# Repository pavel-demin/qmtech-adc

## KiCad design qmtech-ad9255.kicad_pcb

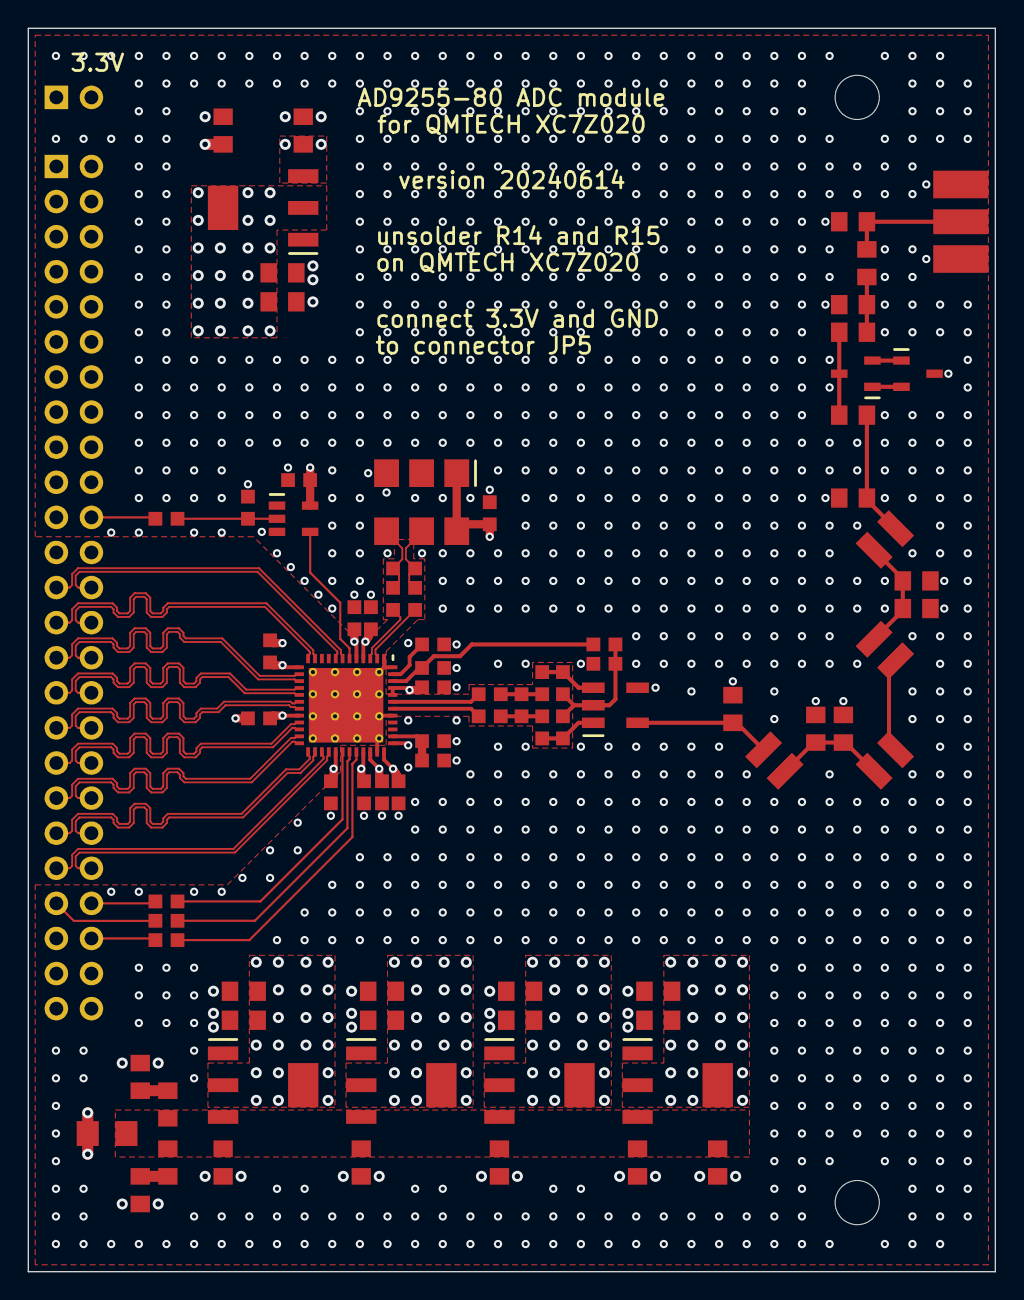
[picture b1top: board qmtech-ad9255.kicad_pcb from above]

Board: 4 copper layers, 70.0 x 90.0 mm, 85 parts (1 on the bottom side), 62 nets.

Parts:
C1, C2, C3, C4, C5, C6, C7, C8, C9, C10, C11, C12, C13, C14, C15, C16, C17, C30: 0603
C18, C19, C20, C21, C22, C23, C24, C25, C26, C27, C28, C29, C33, C34, C35, C36, C37, C38, C39, C40: 0805
CN1: SMA-EDGE
CN2: 2x25
CN3: 1x2
D1, D2: SOT23-3
FB1: 1206
H1, H2: M3
IC1: LFCSP48
IC2, IC3, IC4, IC5, IC6: SOT223-3
IC7: SOT23-5
L1, L2, L3, L4: 1008
R1, R2, R3, R4, R5, R6, R7, R8, R9, R10, R11, R12, R13, R14: 0603
R15, R16, R17, R18, R19, R20, R21, R22, R23, R24, R25, R26: 0805
T1: AT224
Y1: SMD7050-6P

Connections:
5V: C18.1, C20.1, C22.1, C24.1, C28.1, C29.1, FB1.2, IC2.3, IC3.3, IC4.3, IC5.3, R17.1
AIN+: IC1.42, R6.2
AIN-: IC1.43, R7.2
ATT1: CN1.1, R24.1, R25.1
ATT2: C33.1, R24.2, R26.1
AVDD: C6.1, C7.1, C8.1, C9.1, C10.1, C23.1, IC1.4, IC1.5, IC1.34, IC1.36, IC1.44, IC1.45, IC4.2, R20.1
CLK+: C17.1, R9.2, Y1.5
CLK-: C16.1, R9.1, Y1.4
CLKN: C16.2, IC1.3
CLKP: C17.2, IC1.2
CSB1: CN2.46, R12.1
CSB2: IC1.32, R12.2
CVDD: C15.1, C25.1, IC5.2, R21.1, Y1.1, Y1.6
D1N: CN2.27, IC1.11
D1P: CN2.28, IC1.12
D2N: CN2.29, IC1.14
D2P: CN2.30, IC1.15
D3N: CN2.31, IC1.16
D3P: CN2.32, IC1.17
D4N: CN2.33, IC1.18
D4P: CN2.34, IC1.19
D5N: CN2.35, IC1.21
D5P: CN2.36, IC1.22
D6N: CN2.37, IC1.23
D6P: CN2.38, IC1.24
D7N: CN2.39, IC1.25
D7P: CN2.40, IC1.26
DCON: CN2.25, IC1.7
DCOP: CN2.26, IC1.8
DMP1: C28.2, R15.1
DMP2: C29.2, R16.1
DVDD: C12.1, C13.1, C14.1, C19.1, C30.1, IC1.13, IC1.20, IC1.29, IC2.2, IC7.5, R18.1
FLT1: C34.2, C35.1, L1.1
FLT2: C36.1, C37.1, L1.2, L2.1
FLT3: L2.2, L3.1
FLT4: C38.1, C39.1, L3.2, L4.1
FLT5: C40.1, L4.2, T1.6
FLT+: C3.1, R4.2, R6.1
FLT-: C3.2, R5.2, R7.1
GND: C1.2, C2.2, C4.2, C5.2, C6.2, C7.2, C8.2, C9.2, C10.2, C11.2, C12.2, C13.2, C14.2, C15.2, C18.2, C19.2, C20.2, C21.2, C22.2, C23.2, C24.2, C25.2, C26.2, C27.2, C30.2, C35.2, C36.2, C37.2, C38.2, C39.2, C40.2, CN1.2, CN2.1, CN2.2, CN2.47, CN2.48, CN3.1, D2.3, IC1.0, IC1.1, IC1.35, IC1.37, IC1.41, IC1.48, IC2.1, IC3.1, IC4.1, IC5.1, IC6.1, IC7.3, R8.2, R11.2, R15.2, R16.2, R17.2, R18.2, R19.2, R20.2, R21.2, R22.2, R23.2, R25.2, R26.2, T1.4, Y1.3
OEB1: CN2.22, R10.1
OEB2: IC7.2, R10.2, R11.1
OEB3: IC1.6, IC7.4
ORN: CN2.41, IC1.27
ORP: CN2.42, IC1.28
RBIAS: IC1.47, R8.1
SCLK1: CN2.43, R13.1
SCLK2: IC1.31, R13.2
SDIO1: CN2.44, R14.1
SDIO2: IC1.30, R14.2
SEC+: R2.1, R4.1, T1.1
SEC-: R3.1, R5.1, T1.3
SVDD: C11.1, C21.1, IC1.33, IC3.2, R19.1
TVS1: C33.2, C34.1, D1.3
TVS2: D1.1, D2.2
TVS3: D1.2, D2.1
VCCO25: C27.1, CN2.3, CN2.4, IC6.2, R23.1
VCM1: C1.1, IC1.46, R1.1
VCM2: C2.1, R1.2, R2.2, R3.2, T1.2
VIN1: CN2.49, CN2.50, FB1.1
VIN2: C26.1, CN3.2, IC6.3, R22.1
VREF: C4.1, C5.1, IC1.38

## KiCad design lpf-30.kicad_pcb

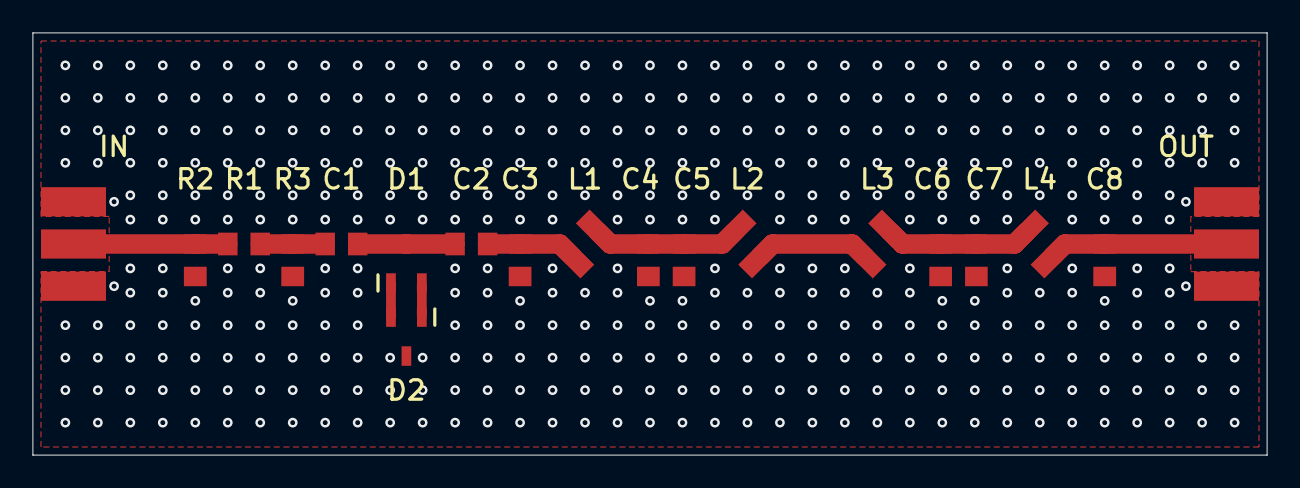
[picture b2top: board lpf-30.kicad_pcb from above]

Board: 2 copper layers, 76.0 x 26.0 mm, 19 parts (0 on the bottom side), 11 nets.

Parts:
C1, C2, C3, C4, C5, C6, C7, C8: 0805
D1, D2: SOT23-3
IN: SMA-EDGE
L1, L2, L3, L4: 1008
OUT: SMA-EDGE
R1, R2, R3: 0805

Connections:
ATT1: IN.1, R1.1, R2.1
ATT2: C1.1, R1.2, R3.1
FLT1: C2.2, C3.1, L1.1
FLT2: C4.1, C5.1, L1.2, L2.1
FLT3: L2.2, L3.1
FLT4: C6.1, C7.1, L3.2, L4.1
FLT5: C8.1, L4.2, OUT.1
GND: C3.2, C4.2, C5.2, C6.2, C7.2, C8.2, D2.3, IN.2, OUT.2, R2.2, R3.2
TVS1: C1.2, C2.1, D1.3
TVS2: D1.1, D2.2
TVS3: D1.2, D2.1

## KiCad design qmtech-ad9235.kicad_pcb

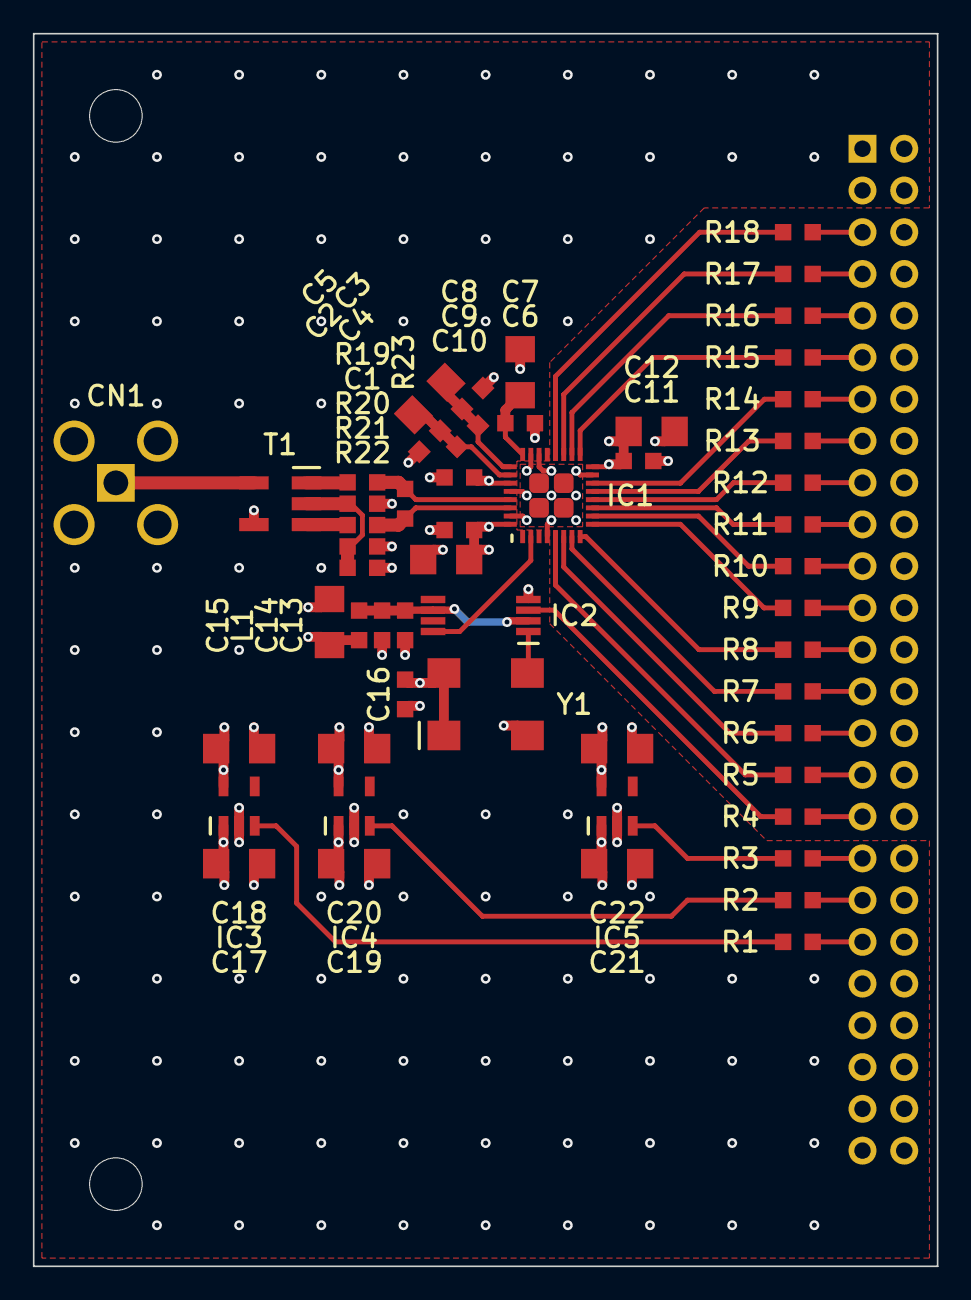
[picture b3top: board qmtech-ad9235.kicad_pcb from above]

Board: 4 copper layers, 55.0 x 75.0 mm, 57 parts (1 on the bottom side), 53 nets.

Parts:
C1, C2, C3, C4, C6, C8, C9, C11, C13, C14, C16: 0603
C5, C7, C10, C12, C15, C17, C18, C19, C20, C21, C22: 1206
CN1: SMA
CN2: 2x25
IC1: LFCSP32
IC2: TSSOP8
IC3, IC4, IC5: SOT23
L1: 0603
M1, M2: M3
R1, R2, R3, R4, R5, R6, R7, R8, R9, R10, R11, R12, R13, R14, R15, R16, R17, R18, R19, R20, R21, R22, R23: 0603
T1: AT224
Y1: SMD7050-4P

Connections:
5V: C17.1, C19.1, C21.1, CN2.49, CN2.50, IC3.1, IC4.1, IC5.1
AEN: IC3.3, R1.1
AVDD: C8.1, C9.1, C10.1, C18.1, IC1.27, IC1.32, IC3.5, R21.1
BVDD: C13.1, C14.1, IC2.2, IC2.6, L1.2
CEN: IC4.3, R2.1
CLK: IC2.1, Y1.3
CVDD: C15.1, C16.1, C20.1, IC4.5, L1.1, Y1.1, Y1.4
D0: IC1.5, R5.1
D1: IC1.6, R6.1
D2: IC1.7, R7.1
D3: IC1.8, R8.1
D4: IC1.9, R9.1
D5: IC1.10, R10.1
D6: IC1.11, R11.1
D7: IC1.12, R12.1
D8: IC1.13, R13.1
D9: IC1.14, R14.1
D10: IC1.17, R15.1
D11: IC1.18, R16.1
D12: IC1.19, R17.1
D13: IC1.20, R18.1
DEN: IC5.3, R3.1
DVDD: C11.1, C12.1, C22.1, IC1.16, IC5.5
GND: C1.2, C2.2, C3.2, C6.2, C7.2, C8.2, C9.2, C10.2, C11.2, C12.2, C13.2, C14.2, C15.2, C16.2, C17.2, C18.2, C19.2, C20.2, C21.2, C22.2, CN1.2, CN2.1, CN2.2, CN2.47, CN2.48, IC1.0, IC1.4, IC1.15, IC1.22, IC1.23, IC1.28, IC1.31, IC2.4, IC3.2, IC4.2, IC5.2, R22.2, T1.4, Y1.2
INPUT: CN1.1, T1.6
REFB: C3.1, C4.2, C5.2, IC1.25
REFT: C2.1, C4.1, C5.1, IC1.26
SEC+: R19.1, T1.1
SEC-: R20.1, T1.3
VCM: C1.1, R21.2, R22.1, T1.2
VIN+: IC1.29, R19.2, R23.1
VIN-: IC1.30, R20.2, R23.2
VREF: C6.1, C7.1, IC1.24
W1: CN2.39, R1.2
W2: CN2.37, R2.2
W3: CN2.35, R3.2
W4: CN2.33, R4.2
W5: CN2.31, R5.2
W6: CN2.29, R6.2
W7: CN2.27, R7.2
W8: CN2.25, R8.2
W9: CN2.23, R9.2
W10: CN2.21, R10.2
W11: CN2.19, R11.2
W12: CN2.17, R12.2
W13: CN2.15, R13.2
W14: CN2.13, R14.2
W15: CN2.11, R15.2
W16: CN2.9, R16.2
W17: CN2.7, R17.2
W18: CN2.5, R18.2
Y0: IC1.2, IC2.8
Y1: IC2.3, R4.1

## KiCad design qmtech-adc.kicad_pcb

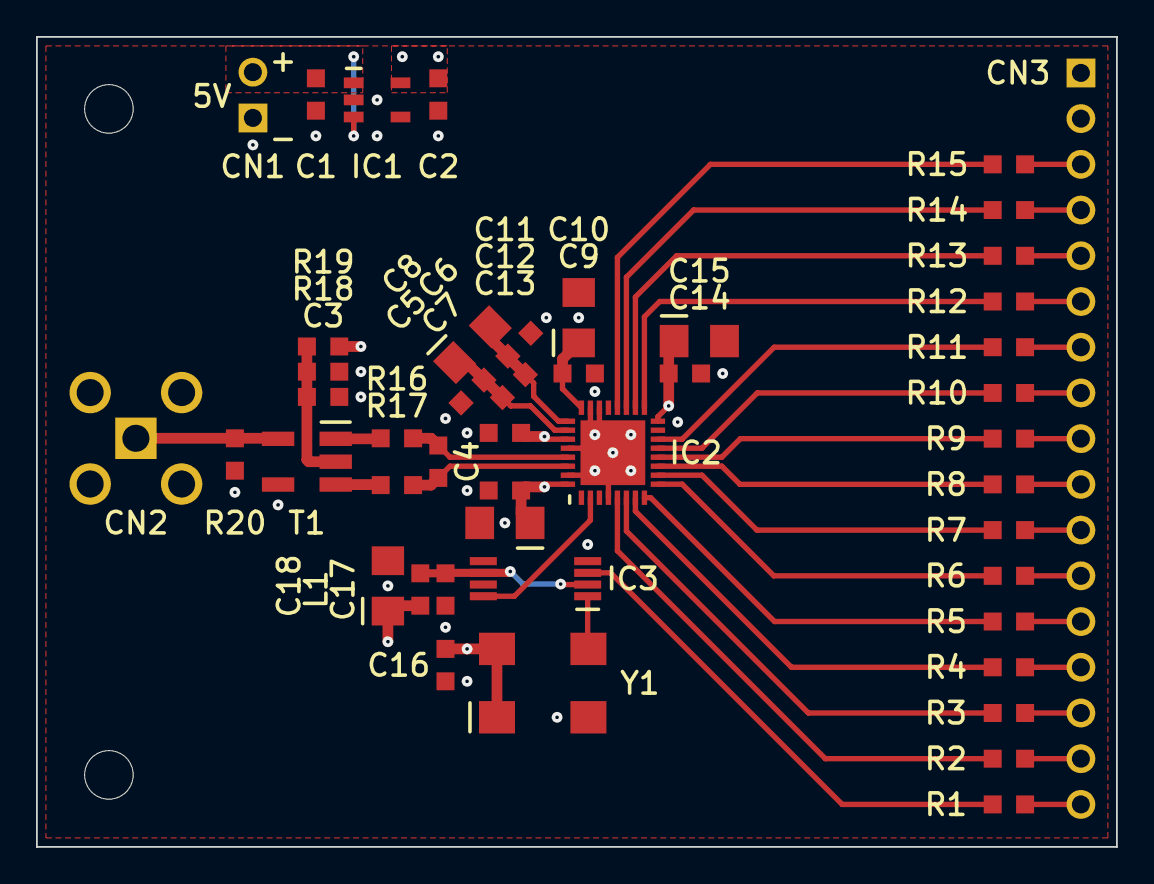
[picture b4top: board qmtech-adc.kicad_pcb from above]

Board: 4 copper layers, 60.0 x 45.0 mm, 49 parts (0 on the bottom side), 46 nets.

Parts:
C1, C2, C3, C4, C5, C6, C7, C9, C11, C12, C14, C16, C17: 0603
C8, C10, C13, C15, C18: CASE-A-3216
CN1: 1x2
CN2: SMA
CN3: 1x17
IC1: SOT23
IC2: LFCSP32
IC3: TSSOP8
L1: 0603
M1, M2: M25
R1, R2, R3, R4, R5, R6, R7, R8, R9, R10, R11, R12, R13, R14, R15, R16, R17, R18, R19, R20: 0603
T1: AT224
Y1: 7050

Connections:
5V: C1.1, CN1.2, IC1.1, IC1.3
AVDD: C2.1, C11.1, C12.1, C13.1, C16.1, C18.1, IC1.5, IC2.27, IC2.32, L1.1, R18.1, Y1.1, Y1.4
BVDD: C17.1, IC3.2, IC3.6, L1.2
CLK: IC3.1, Y1.3
D0: IC2.5, R2.1
D1: IC2.6, R3.1
D2: IC2.7, R4.1
D3: IC2.8, R5.1
D4: IC2.9, R6.1
D5: IC2.10, R7.1
D6: IC2.11, R8.1
D7: IC2.12, R9.1
D8: IC2.13, R10.1
D9: IC2.14, R11.1
D10: IC2.17, R12.1
D11: IC2.18, R13.1
D12: IC2.19, R14.1
D13: IC2.20, R15.1
DVDD: C14.1, C15.1, CN3.3, IC2.16
GND: C1.2, C2.2, C3.2, C5.2, C6.2, C9.2, C10.2, C11.2, C12.2, C13.2, C14.2, C15.2, C16.2, C17.2, C18.2, CN1.1, CN2.2, CN3.1, IC1.2, IC1.4, IC2.4, IC2.15, IC2.22, IC2.23, IC2.28, IC2.31, IC2.33, IC3.4, R19.2, R20.2, T1.4, Y1.2
INPUT: CN2.1, R20.1, T1.6
REFB: C6.1, C7.2, C8.2, IC2.25
REFT: C5.1, C7.1, C8.1, IC2.26
SEC+: R16.1, T1.1
SEC-: R17.1, T1.3
VCM: C3.1, R18.2, R19.1, T1.2
VIN+: C4.1, IC2.29, R16.2
VIN-: C4.2, IC2.30, R17.2
VREF: C9.1, C10.1, IC2.24
W1: CN3.33, R1.2
W2: CN3.31, R2.2
W3: CN3.29, R3.2
W4: CN3.27, R4.2
W5: CN3.25, R5.2
W6: CN3.23, R6.2
W7: CN3.21, R7.2
W8: CN3.19, R8.2
W9: CN3.17, R9.2
W10: CN3.15, R10.2
W11: CN3.13, R11.2
W12: CN3.11, R12.2
W13: CN3.9, R13.2
W14: CN3.7, R14.2
W15: CN3.5, R15.2
Y0: IC2.2, IC3.8
Y1: IC3.3, R1.1

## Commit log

2024-03-31 replace C1952781 with C7171
2024-03-31 add qmtech-adc.kicad_pro
2024-04-01 use 0.8 mm tracks for input signal
2024-04-05 rename qmtech-adc to qmtech-ad9235
2024-04-07 replace M25 with M3
2024-04-07 reduce length of output traces
2024-04-07 improve AVDD and GND connections
2024-04-07 replace 1x17 with 2x25
2024-04-07 add DVDD regulator
2024-04-07 improve LFCSP32
2024-04-07 add CVDD regulator
2024-04-07 fix part numbers
2024-04-07 reduce PCB width
2024-04-07 replace 1uF and 10uF tantalum capacitors with 10uF ceramic capacitors
2024-04-07 improve vias
2024-04-07 set thermal bridge width to 0.6
2024-04-07 increase pin header pads hole size
2024-04-08 add GND vias
2024-04-08 increase SMA pads hole size
2024-04-09 add 1uF decoupling capacitor for clock buffer
2024-04-09 improve position of PCB on page
2024-04-09 add 1206 footprint
2024-04-10 set pin header pad hole size to 1.7
2024-04-10 add qmtech-ad9255
2024-04-10 fix GND vias and disconnect unused regulator pin in qmtech-ad9235
2024-04-10 update CN2 in qmtech-ad9235
2024-04-10 improve qmtech-ad9235
2024-04-10 fix 1206
2024-04-10 rename 7050 to SMD7050-4P
2024-04-10 set via hole diameter to 0.3
2024-04-11 improve LFCSP32 exposed pad
2024-04-11 move M3 holes away from edge
2024-04-11 improve DVDD decoupling in qmtech-ad9235
2024-04-11 add GND plane cutout around data traces in qmtech-ad9235
2024-04-11 improve ground and power planes in qmtech-ad9235
2024-04-11 move VCM closer to transformer in qmtech-ad9235
2024-04-12 add resistors to FPGA outputs in qmtech-ad9235
2024-04-12 simplify input circuit in qmtech-ad9235
2024-04-12 update numbers in capacitor reference designators in qmtech-ad9235
2024-04-12 update numbers in resistor reference designators in qmtech-ad9235
2024-04-12 improve qmtech-ad9255
2024-04-12 add GND vias to qmtech-ad9255
2024-04-12 update Y1 footprint in qmtech-ad9255
2024-04-12 add SMD3225-6P
2024-04-12 replace C5179991 with C5247989 in qmtech-ad9255
2024-04-13 improve differential traces in qmtech-ad9255
2024-04-13 align R1 and R2 in qmtech-ad9255
2024-04-13 set part number for R1 to C23185 in qmtech-ad9255
2024-04-13 set width of clock traces to 0.3 in qmtech-ad9255
2024-04-13 add resistors to SPI inputs in qmtech-ad9255
2024-04-13 improve CN3 pin designation
2024-04-14 update constraints in qmtech-ad9255
2024-04-14 replace SMA through-hole connector with SMA edge connector in qmtech-ad9255
2024-04-14 increase distance between traces and vias in qmtech-ad9255
2024-04-15 fix SMA
2024-04-15 replace C23345 with C22859 in qmtech-ad9255
2024-04-15 improve CVDD in qmtech-ad9255
2024-04-15 increase distance between C10 and traces in qmtech-ad9255
2024-04-15 add GND vias around regulators in qmtech-ad9255
2024-04-17 hide all reference designators in qmtech-ad9255
2024-04-17 add module name and instructions to qmtech-ad9255
2024-04-18 reorganize differential traces in qmtech-ad9255
2024-04-18 remove unconnected annular rings in qmtech-ad9255
2024-04-18 set thermal relief gap to 0.3 in qmtech-ad9255
2024-04-18 improve 1x2 and 2x25
2024-04-18 update 1x2 and 2x25 in qmtech-ad9255
2024-04-19 set copper to hole clearance to 2.6 in qmtech-ad9255
2024-04-19 improve clock traces in qmtech-ad9255
2024-04-19 improve power planes in qmtech-ad9255
2024-04-19 add 10uF AVDD decoupling capacitor to qmtech-ad9255
2024-04-19 add GND zone cutout around input traces in qmtech-ad9255
2024-04-19 increase distance between pin header and ADC in qmtech-ad9255
2024-04-19 set part number for R2 to C23025 in qmtech-ad9255
2024-04-20 reorganize input components in qmtech-ad9255
2024-04-20 set part number for R1 to C22775 in qmtech-ad9255
2024-04-20 reorganize power planes in qmtech-ad9255
2024-04-21 align IC2 and IC5 in qmtech-ad9255
2024-04-21 add notebooks
2024-04-22 reorganize resistors at ADC input in qmtech-ad9255
2024-04-22 add AVDD decoupling capacitors to qmtech-ad9255
2024-04-22 set part number for R5 to C25804 in qmtech-ad9255
2024-04-22 rotate VREF decoupling capacitors in qmtech-ad9255
2024-04-22 set part number for C1 to C15849 in qmtech-ad9255
2024-04-24 improve power system in qmtech-ad9255
2024-04-25 set part number for R9 to C17928 in qmtech-ad9255
2024-04-27 add capacitor discharge resistors to qmtech-ad9255
2024-04-28 set part number for R12 to C25804 in qmtech-ad9255
2024-04-29 remove redundant 10uF capacitors from qmtech-ad9255
2024-04-29 set part number for Y1 to C5179988 in qmtech-ad9255
2024-04-29 set part number for R8 to C21190 in qmtech-ad9255
2024-04-29 replace R9 with FB1 in qmtech-ad9255
2024-04-29 remove vias from regulators inputs and outputs in qmtech-ad9255
2024-04-30 improve traces in qmtech-ad9255
2024-04-30 replace 1206 with 0805 in qmtech-ad9255
2024-04-30 improve LVDS traces in qmtech-ad9255
2024-05-01 add shunt capacitor to ADC input in qmtech-ad9255
2024-05-01 replace C440198 with C15850 in qmtech-ad9255
2024-05-01 improve VIN filter in qmtech-ad9255
2024-05-01 equalize length of LVDS traces in qmtech-ad9255
2024-05-01 improve 1206 in qmtech-ad9255
2024-05-01 set part number for R1 to C23197 in qmtech-ad9255
2024-05-02 improve CVDD decoupling in qmtech-ad9255
2024-05-02 set part number for R2 and R3 to C22808 in qmtech-ad9255
2024-05-02 update version in qmtech-ad9255
2024-05-02 improve GND connection of SMA connector in qmtech-ad9255
2024-05-02 add GND via to qmtech-ad9255
2024-05-02 improve top GND zone in qmtech-ad9255
2024-05-03 add VCCO33 filter to qmtech-ad9255
2024-05-03 improve SPI traces in qmtech-ad9255
2024-05-03 improve connections to decoupling capacitors in qmtech-ad9255
2024-05-04 improve 5V and VCCO33 filters in qmtech-ad9255
2024-05-11 add SOT23-3
2024-05-11 add 1008
2024-05-11 add lpf-30
2024-05-13 improve lpf-30
2024-05-14 improve 0805
2024-05-14 improve 1008
2024-05-14 replace 0603 with 0805 in lpf-30
2024-05-15 improve SOT23
2024-05-16 improve AT224
2024-05-16 add 30 MHz LPF and other improvements to qmtech-ad9255
2024-05-17 improve LFCSP48
2024-05-17 update SOT23-3 in lpf-30
2024-05-18 improve 30 MHz LPF in qmtech-ad9255
2024-05-20 improve mounting hole positions in qmtech-ad9255
2024-05-24 improve SMA-EDGE
2024-05-25 add SOT223-3
2024-05-25 replace TPS7A20 with TLV1117LV in qmtech-ad9255
2024-05-28 rename IN1 to OEB1 in qmtech-ad9255
2024-05-28 fix filter shield frame in qmtech-ad9255
2024-05-31 add thermal reliefs to all zones in qmtech-ad9255
2024-05-31 increase size of zones under regulators in qmtech-ad9255
2024-05-31 move VIN1 and 5V zones to front layer in qmtech-ad9255
2024-06-02 set part number for R22 to C17414 in qmtech-ad9255
2024-06-03 reduce filter shield frame width in qmtech-ad9255
2024-06-14 remove qmtech-ad9235
2024-07-30 add enclosure by S53ZO
